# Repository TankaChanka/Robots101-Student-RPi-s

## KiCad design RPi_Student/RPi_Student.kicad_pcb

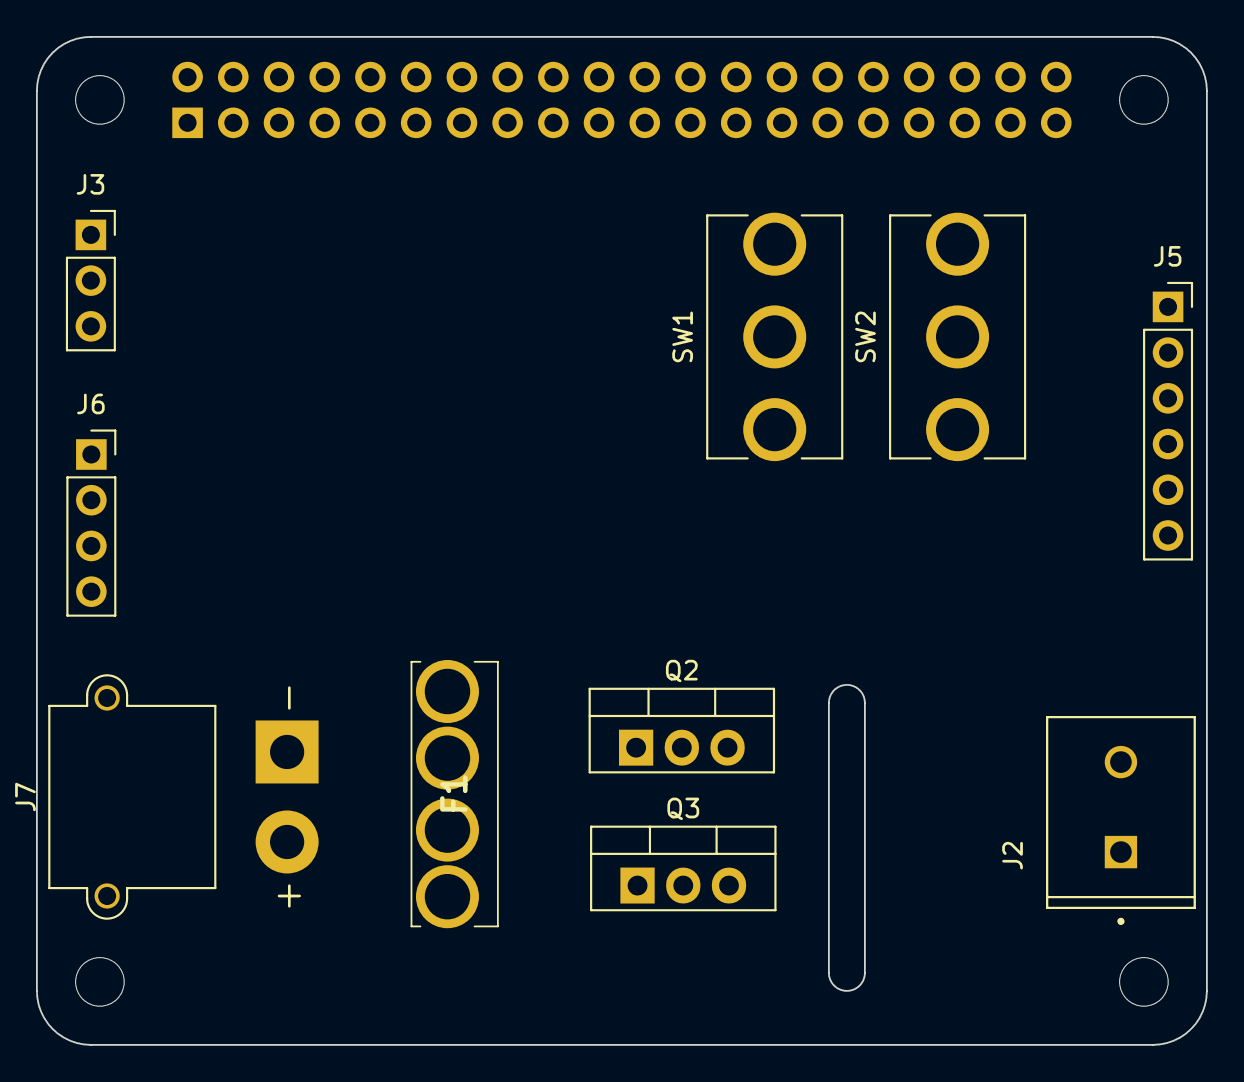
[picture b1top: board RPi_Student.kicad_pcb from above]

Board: 2 copper layers, 65.0 x 56.0 mm, 15 parts (1 on the bottom side), 14 nets.

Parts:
F1: MCCQ-122; MCCQ122
J2: Conn_01x02; TE_282836-2
J3: Conn_01x03; PinSocket_1x03_P2.54mm_Vertical
J4: GPIO; PinSocket_2x20_P2.54mm_Vertical
J5: Conn_01x06; PinSocket_1x06_P2.54mm_Vertical
J6: Conn_01x04; PinSocket_1x04_P2.54mm_Vertical
J7: Conn_01x02_Male; AMASS_XT30PW-M_1x02_P2.50mm_Horizontal
MH1, MH2, MH3, MH4: MountingHole_2.7mm_M2.5
Q2, Q3: IRF9540N; TO-220-3_Vertical
SW1, SW2: SW_SPDT; Switch_SPDT_Jaycar

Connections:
+3V3: J4.1, J6.1
+5V: J4.2, J4.4
+BATT: J2.1, SW2.1 (A)
/GPIO2/SDA1: J4.3, J5.6
/GPIO3/SCL1: J4.5, J5.5
/GPIO4/GPCLK: J4.7, J5.2
/GPIO9/MISO: J4.21, J5.1
/GPIO17/GEN0: J4.11, J6.2
/GPIO18/GEN1: J3.1, J4.12
/GPIO27/GEN2: J4.13, J6.3
GND: J2.2, J3.3, J4.6, J4.9, J4.14, J4.20, J4.25, J4.30, J4.34, J4.39, J5.3, J6.4, J7.1, Q3.1 (G)
unnamed: F1.1, F1.2, J7.2
unnamed: F1.3, F1.4, Q3.2 (D)
unnamed: Q3.3 (S), SW1.2 (B), SW2.2 (B)

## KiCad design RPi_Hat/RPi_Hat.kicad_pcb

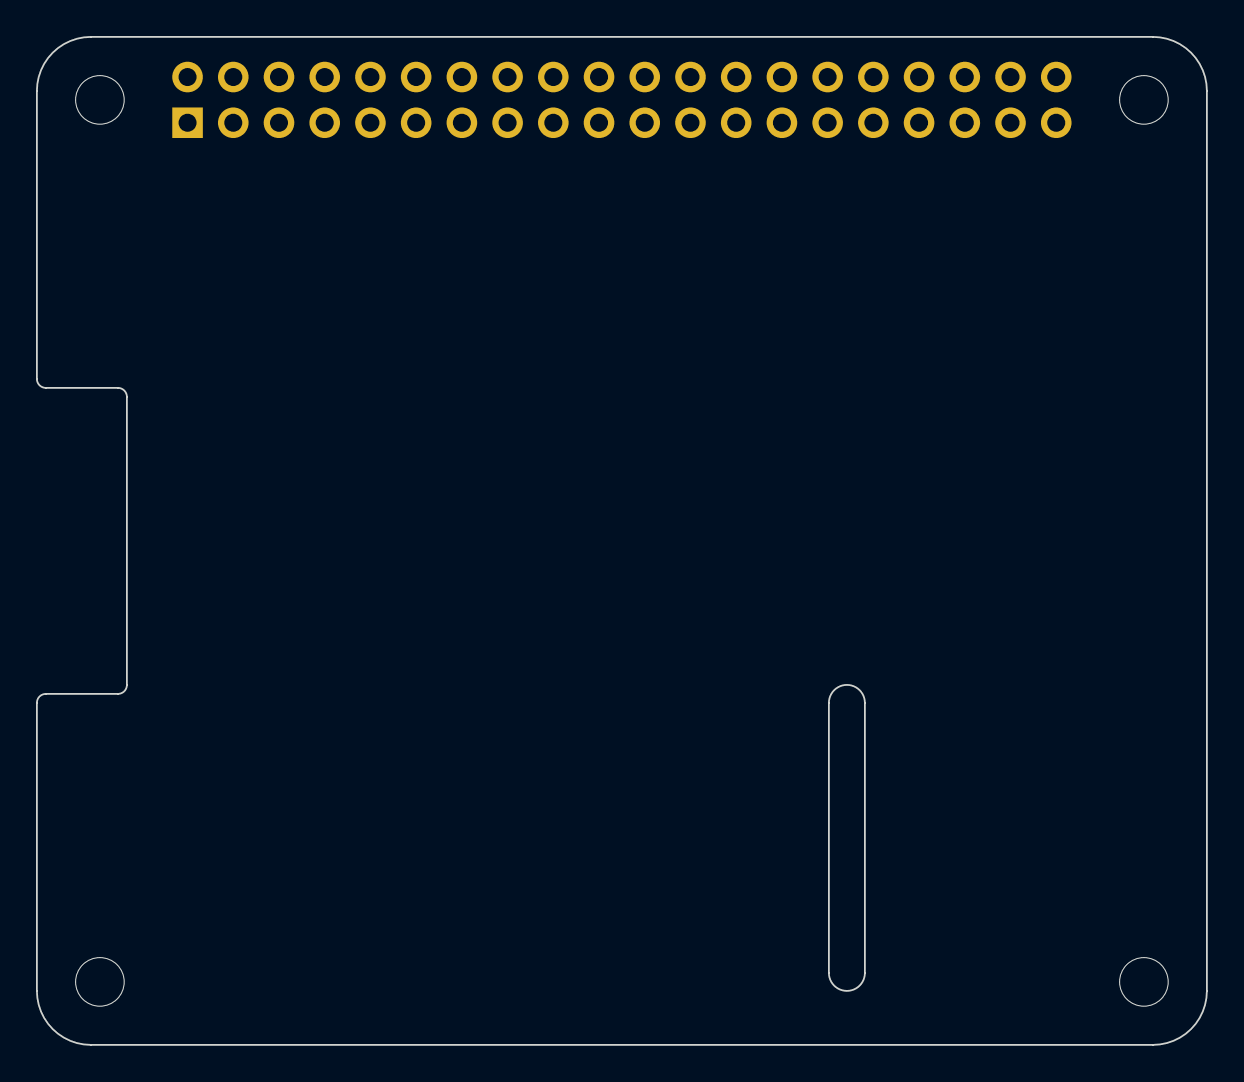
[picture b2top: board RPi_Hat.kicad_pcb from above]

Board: 2 copper layers, 65.0 x 56.0 mm, 5 parts (1 on the bottom side), 3 nets, no tracks yet.

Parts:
J1: GPIO; PinSocket_2x20_P2.54mm_Vertical
MH1, MH2, MH3, MH4: MountingHole_2.7mm_M2.5

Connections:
+3V3: J1.1, J1.17
+5V: J1.2, J1.4
GND: J1.6, J1.9, J1.14, J1.20, J1.25, J1.30, J1.34, J1.39

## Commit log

2023-03-28 Created student content - awaiting test
2023-03-28 Now added official library needed
2023-04-04 Updated to account for new PCB design changes
2023-04-04 New layout for students to solve
